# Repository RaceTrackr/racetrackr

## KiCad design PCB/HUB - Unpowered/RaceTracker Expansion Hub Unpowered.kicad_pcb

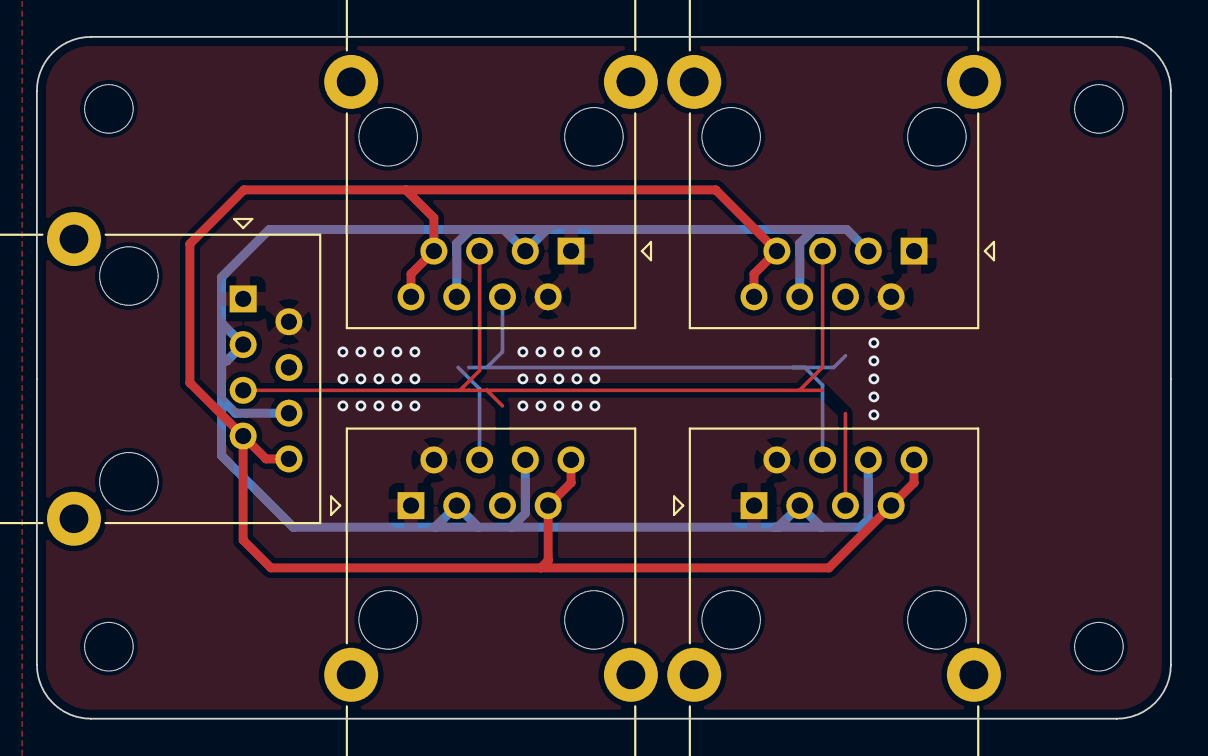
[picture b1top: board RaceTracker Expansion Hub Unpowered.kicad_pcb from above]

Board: 2 copper layers, 63.0 x 37.9 mm, 5 parts (0 on the bottom side), 5 nets.

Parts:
J1, J2, J3, J4, J5: RJ45; RJ45_Ninigi_GE

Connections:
+5V: J1.3, J1.6, J2.3, J2.6, J3.3, J3.6, J4.3, J4.6, J5.3, J5.6
+12V: J1.7, J1.8, J2.7, J2.8, J3.7, J3.8, J4.7, J4.8, J5.7, J5.8
CAN_H: J1.5, J2.5, J3.5, J4.5, J5.5
CAN_L: J1.4, J2.4, J3.4, J4.4, J5.4
GND: J1.1, J1.2, J2.1, J2.2, J3.1, J3.2, J4.1, J4.2, J5.1, J5.2

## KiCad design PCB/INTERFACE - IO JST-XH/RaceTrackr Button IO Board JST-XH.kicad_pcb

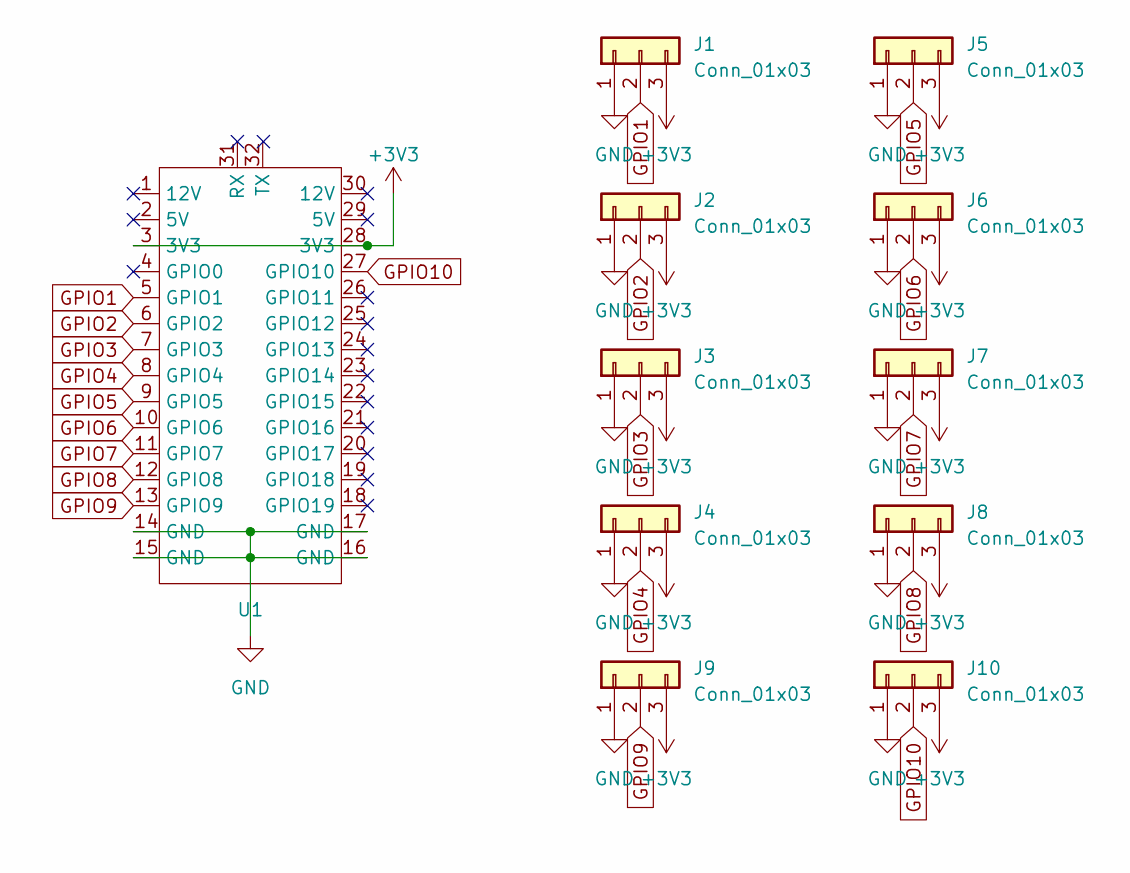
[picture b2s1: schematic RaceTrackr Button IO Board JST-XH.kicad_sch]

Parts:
J1, J2, J3, J4, J5, J6, J7, J8, J9, J10: Conn_01x03; JST_XH_B3B-XH-A_1x03_P2.50mm_Vertical
U1: RaceTrackr Interface Board Reference

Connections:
+3V3: J1.3, J2.3, J3.3, J4.3, J5.3, J6.3, J7.3, J8.3, J9.3, J10.3, U1.3 (3V3), U1.28 (3V3)
GND: J1.1, J2.1, J3.1, J4.1, J5.1, J6.1, J7.1, J8.1, J9.1, J10.1, U1.14 (GND), U1.15 (GND), U1.16 (GND), U1.17 (GND)
GPIO1: J1.2, U1.5 (GPIO1)
GPIO2: J2.2, U1.6 (GPIO2)
GPIO3: J3.2, U1.7 (GPIO3)
GPIO4: J4.2, U1.8 (GPIO4)
GPIO5: J5.2, U1.9 (GPIO5)
GPIO6: J6.2, U1.10 (GPIO6)
GPIO7: J7.2, U1.11 (GPIO7)
GPIO8: J8.2, U1.12 (GPIO8)
GPIO9: J9.2, U1.13 (GPIO9)
GPIO10: J10.2, U1.27 (GPIO10)

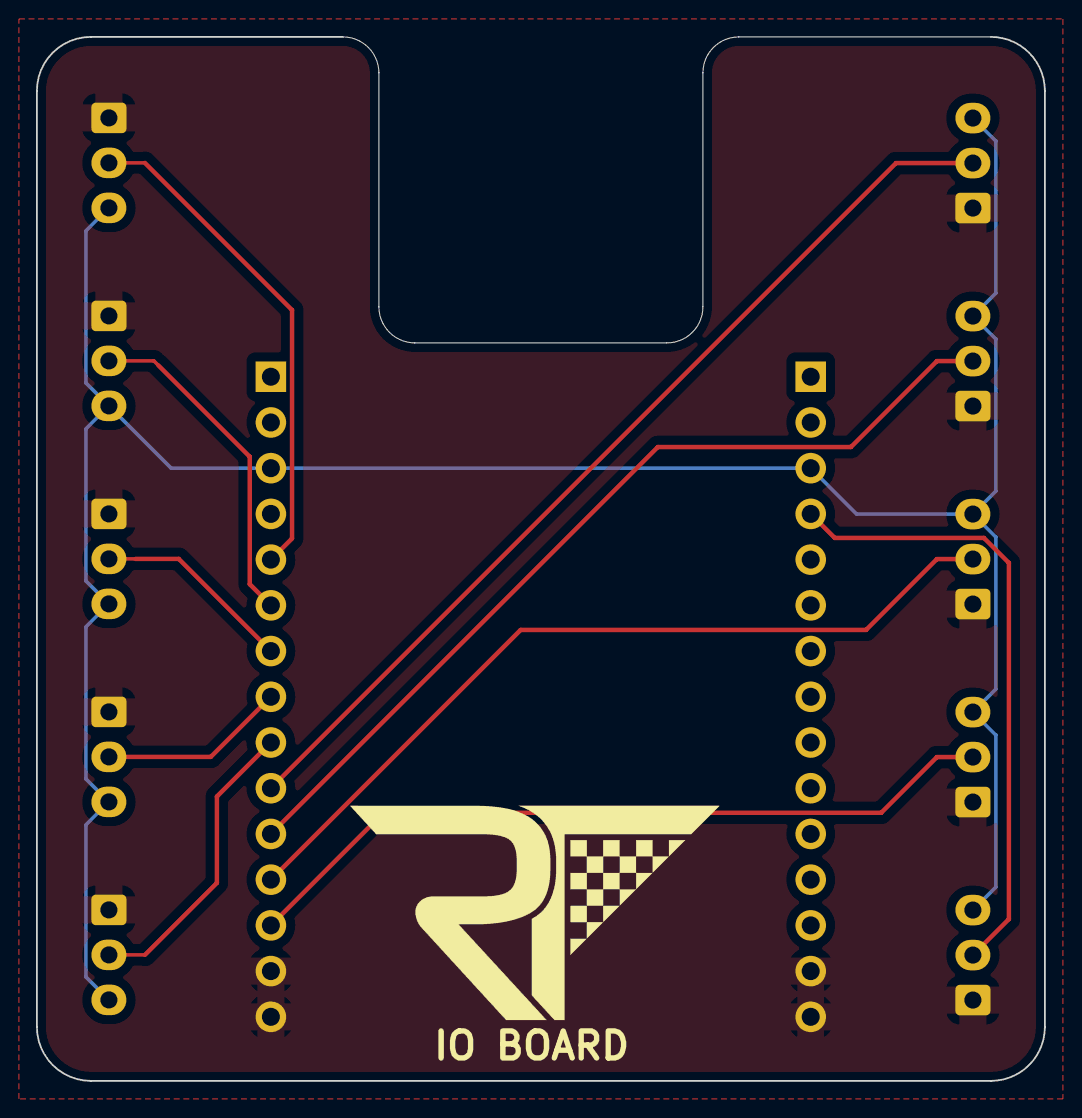
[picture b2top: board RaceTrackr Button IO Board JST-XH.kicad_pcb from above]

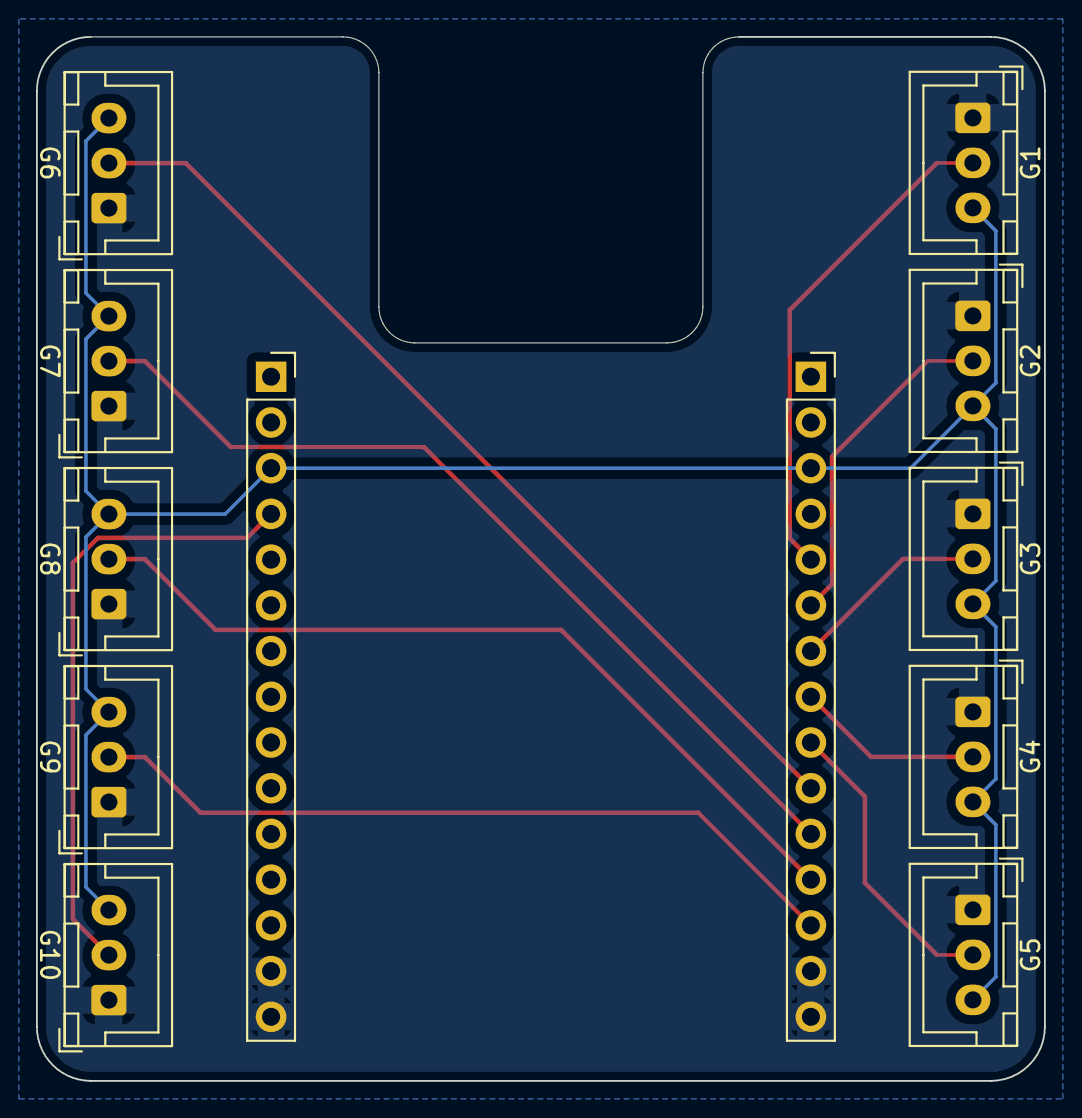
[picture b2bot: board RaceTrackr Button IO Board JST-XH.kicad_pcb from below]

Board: 2 copper layers, 56.0 x 58.0 mm, 11 parts (10 on the bottom side), 12 nets.

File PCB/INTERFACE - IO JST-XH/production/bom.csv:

Designator,Footprint,Quantity,Value,LCSC Part #
"J1, J10, J2, J3, J4, J5, J6, J7, J8, J9",JST_XH_B3B-XH-A_1x03_P2.50mm_Vertical,10,Conn_01x03,
U1,RaceTrackr Interface Board Reference,1,~,

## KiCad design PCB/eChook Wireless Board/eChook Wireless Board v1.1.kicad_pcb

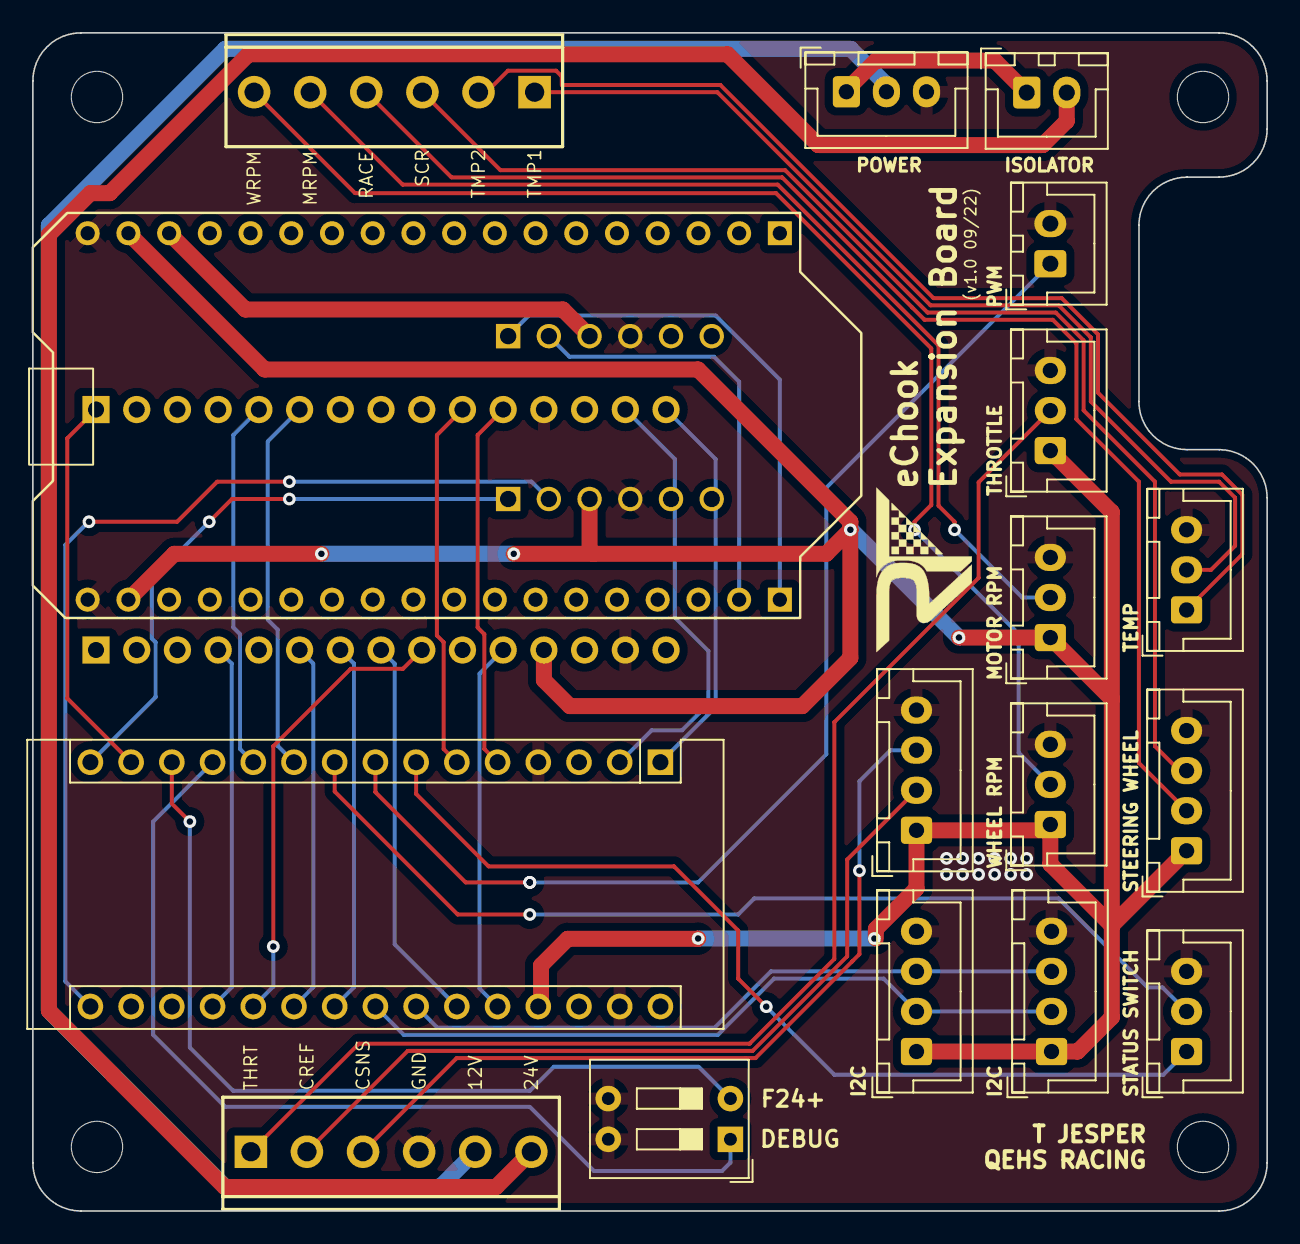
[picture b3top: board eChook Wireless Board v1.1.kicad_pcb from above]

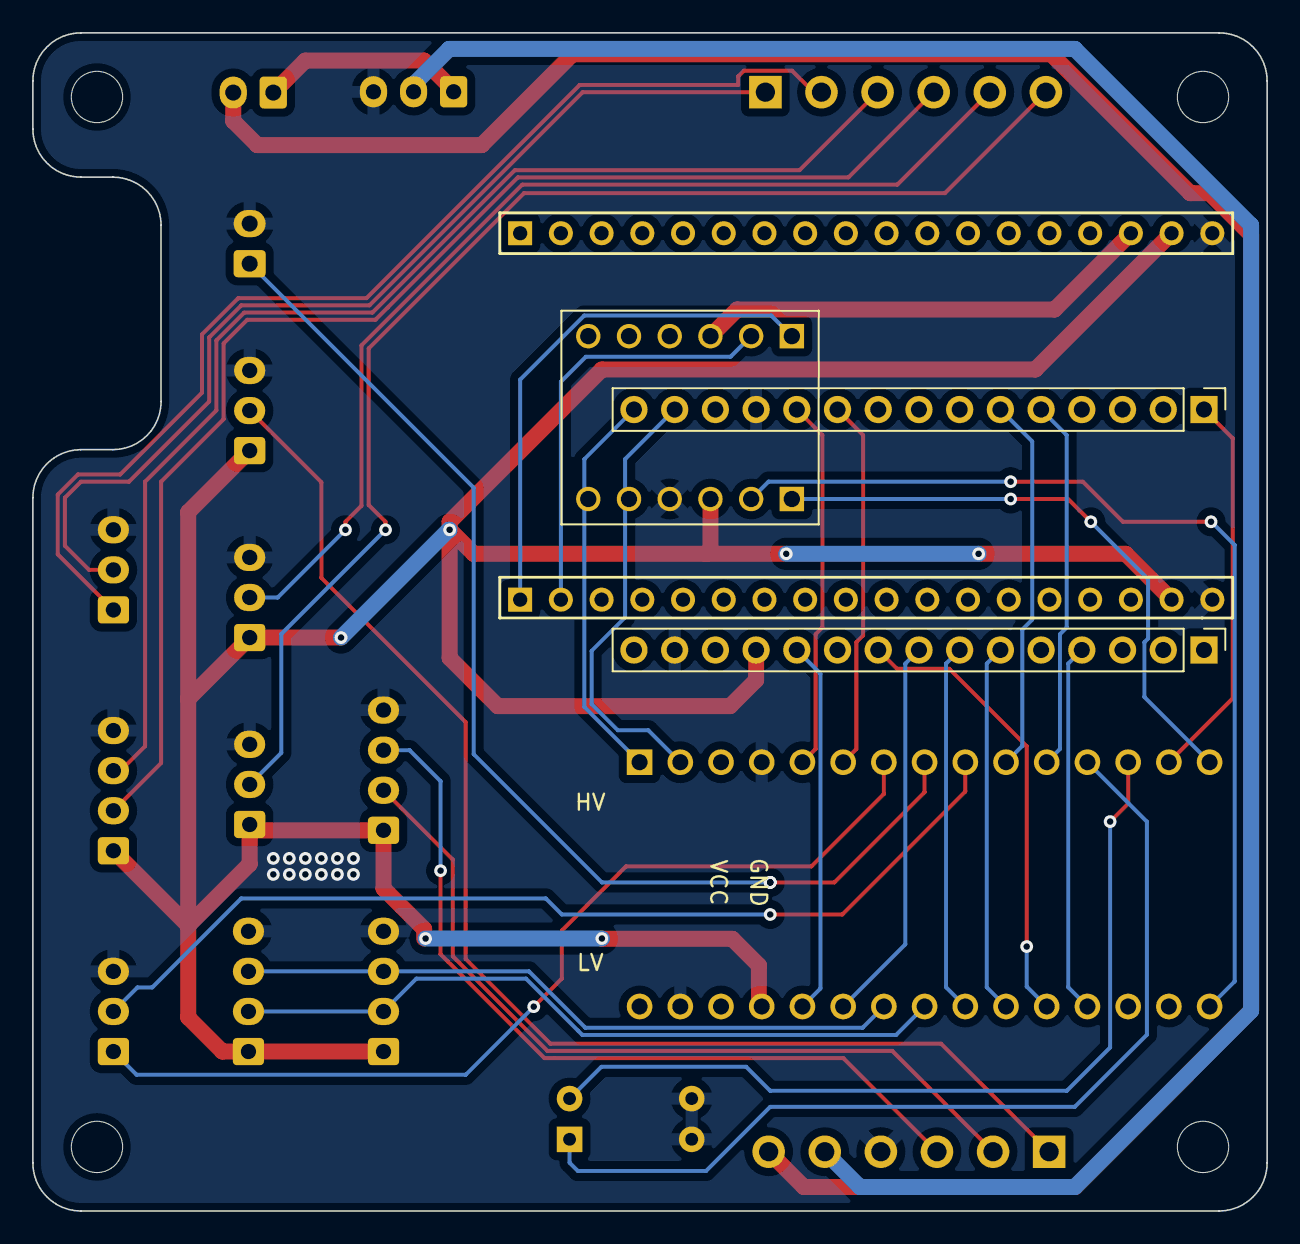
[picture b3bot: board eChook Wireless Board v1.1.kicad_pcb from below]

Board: 2 copper layers, 77.0 x 73.5 mm, 24 parts (3 on the bottom side), 39 nets.

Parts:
A: MountingHole_3.2mm_M3
A1: Arduino_Nano_v3.x; Arduino_Nano
B: MountingHole_3.2mm_M3
C: MountingHole_3.2mm_M3
D: MountingHole_3.2mm_M3
J1: POWER_CONNECTION; JST_XH_B3B-XH-A_1x03_P2.50mm_Vertical
J2: POWER_SWITCH; JST_XH_B2B-XH-A_1x02_P2.50mm_Vertical
J3: PWM_OUTPUT_CONN; JST_XH_B2B-XH-A_1x02_P2.50mm_Vertical
J4, J7: Conn_01x15_Male; PinHeader_1x15_P2.54mm_Vertical
J5: THROTTLE_CONNECTION; JST_XH_B3B-XH-A_1x03_P2.50mm_Vertical
J6: I2C_1_CONN; JST_XH_B4B-XH-A_1x04_P2.50mm_Vertical
J8: I2C_2_CONN; JST_XH_B4B-XH-A_1x04_P2.50mm_Vertical
J9: MOTOR_RPM_CONNECTION; JST_XH_B3B-XH-A_1x03_P2.50mm_Vertical
J10: WHEEL_RPM_CONNECTION; JST_XH_B3B-XH-A_1x03_P2.50mm_Vertical
J12: STATUS_CONNECTION; JST_XH_B3B-XH-A_1x03_P2.50mm_Vertical
J13: CURRENT_CONN; JST_XH_B4B-XH-A_1x04_P2.50mm_Vertical
J14: TEMP_CONNECTION; JST_XH_B3B-XH-A_1x03_P2.50mm_Vertical
J15: WHEEL_CONN; JST_XH_B4B-XH-A_1x04_P2.50mm_Vertical
J16, J17: Screw_Terminal_01x06; SCREWTERMINAL-3.5MM-6
SW1: SW_DIP_x02; SW_DIP_SPSTx02_Slide_9.78x7.26mm_W7.62mm_P2.54mm
U1: LogicLevelConverter; CONV_BOB-12009
U2: ESP32_LoRa; ESP32 LoRa

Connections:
12_B2B: J1.2, J16.5
24_B2B: J2.2, J16.6
+3V3: U1.LV, U2.16 (3V3)
+5V: A1.27 (+5V), J4.12, J5.1, J6.1, J8.1, J9.1, J10.1, J13.1, J15.1, U1.HV, U2.17 (5V), U2.20 (5V)
/+24V_ISOLATED: J1.1, J2.1
BATT_1: A1.26 (A7), J4.11
BATT_T: A1.19 (A0), J4.4
BRAKE: A1.10 (D7), J7.6
BT_IN: A1.2 (D0/RX), J7.14
BT_OUT: A1.1 (D1/TX), J7.15
CREF_B2B: J13.2, J16.2
CSENSE_B2B: J13.3, J16.3
CURRENT: A1.21 (A2), J4.6
DEBUG_MODE: A1.12 (D9), SW1.1
F24_MODE: A1.13 (D10), SW1.2
GND: A1.4 (GND), A1.29 (GND), J1.3, J3.2, J4.14, J5.3, J6.4, J7.12, J8.4, J9.3, J10.3, J12.3, J13.4, J14.3, J15.4, J16.4, SW1.3, SW1.4, U1.GND_1 (GND), U1.GND_2 (GND), U2.18 (GND), U2.19 (GND)
MOTOR_PWM: A1.8 (D5), J3.1
MOTOR_RPM: A1.5 (D2), J7.11
MRPM_B2B: J9.2, J17.5
RACE_START: A1.11 (D8), J7.5
RACE_START_B2B: J15.2, J17.4
RACE_SWITCH: A1.7 (D4), J12.1
RX_HIGH: A1.16 (D13), U1.HV2
RX_LOW: U1.LV1, U2.36 (GPIO16)
SCL: A1.24 (A5), J6.3, J8.3
SCREEN_SWITCH: A1.14 (D11), J7.1
SCREEN_SWITCH_B2B: J15.3, J17.3
SDA: A1.23 (A4), J6.2, J8.2
TELEMETRY_SWITCH: A1.9 (D6), J12.2
TEMP1_B2B: J14.1, J17.2
TEMP2_B2B: J14.2, J17.1
TEMP_1: A1.20 (A1), J4.9
TEMP_2: A1.25 (A6), J4.8
THROTTLE: A1.22 (A3), J4.7
THROTTLE_B2B: J5.2, J16.1
TX_HIGH: A1.15 (D12), U1.HV1
TX_LOW: U1.LV2, U2.35 (GPIO17)
WHEEL_RPM: A1.6 (D3), J7.10
WRPM_B2B: J10.2, J17.6
